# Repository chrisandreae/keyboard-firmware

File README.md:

# Programmable keyboard firmware
**(c) 2012-2014 Chris Andreae**

An extensively programmable USB keyboard firmware for AVR microcontrollers, easily adaptable to new keyboard hardware.

## Features

 * Dynamically reprogrammable two-layer layout (one for the main keyboard, and one for the keypad), with layer switching via a 'keypad' key
 * Also appears as USB mouse (whose functions can be bound to keys)
 * Onboard layout profiles to save/restore up to ten separate programmed
   keyboard layouts.
 * Buzzer audio support (included in Kinesis hardware)
 * USB API for configuring, remapping and uploading programs to the keyboard. (C++ Qt4-based GUI client and Ruby library included.)
 * Enhanced text macros that fully support modifier keys and can be triggered by any combination of up to four keys <sup>[*](#myfootnote1)</sup>
 * Programming, macro recording and layout backup save/load can be performed entirely on-keyboard with no additional software <sup>[*](#myfootnote1)</sup>
 * Built-in virtual machine interpreter for running up to six concurrent independent tasks <sup>[*](#myfootnote1)</sup>

<a name="myfootnote1">*</a>: This feature requires an external AT24C164 or compatible EEPROM (already built into Kinesis Advantage and Kinesis Advantage Pro keyboards).

## Currently Supported Keyboards

For now, the firmware supports various keyboard models:
 * Out of the box:
   * Ergodox
 * With drop-in microcontroller replacement (see schematic/ dir):
   * various Kinesis contoured ergonomic keyboards
     * Kinesis Contoured (tested on model 110; should also support models 100, 120 and 130)
     * Kinesis Advantage & Kinesis Advantage Pro (models 500 and 510)
 PR are welcome to extend support to other keyboards!

+### Drop-in microcontroller replacement
The drop-in microcontroller replacement can be built using most ATMega series AVR microcontrollers. The firmware accesses it via either LUFA (if native USB is available) or VUSB.

## Compiling

To compile the project for a non-USB-capable AVR using the V-USB library:

````make -f Makefile.vusb HARDWARE_VARIANT=<variant>````

Currently supported hardware variants for non-USB AVRs are:

* ````KINESIS```` (Kinesis Advantage/Professional, ATMega32, board design in schematic/Kinesis{Advantage/Professional})
* ````KINESIS110```` (Kinesis Model 110, ATMega32, board design in schematic/KinesisModel110)

To compile the project for a USB-capable AVR using the LUFA library:

````make -f Makefile.lufa HARDWARE_VARIANT=<variant> HAS_EXTERNAL_STORAGE={1,0}````

Currently supported hardware variants for USB AVRs are:

* ````ERGODOX```` (Ergodox, ATMega32u4 (Teensy))

## Usage

The default key layout for each hardware type can be found in the subdirectory ````layouts/````

### Enter/exit layout programming

Kinesis: ````Program + F12````

Ergodox: ````Program + P````

Press the above key combination to enter programming mode. In programming mode,
first press a source key to select the action of that key in the default
layout. Then, press a destination key to assign the selected action to. Repeat
source and destination keys as desired to continue remapping. The keypad key may
be pressed at any time to switch layers, in order to allow copying keys between
layers. The keypad and program keys may not be themselves remapped. When done,
press the above programming-mode key combination to leave programming mode.

### Layout backup saving/loading

* Save current layout to backup slot   = ````Progrm + S + [1 - 0]````
* Restore layout from backup slot      = ````Progrm + L + [1 - 0]````
* Delete saved layout from backup slot = ````Progrm + D + [1 - 0]````

In addition to the current layout, you can create up to 10 independent backup layouts.
Backup layouts allow you to rapidly switch between different keyboard mapping configurations.
Each backup layout slot is associated with a number key from ````1```` to ````0````. Layouts are
stored as their difference from the factory-default layout: the more keys that are
remapped from their default positions, the more space that a backup layout will consume.
In total, there is space for 256 key remappings shared between all backup layouts.

### Reset to default layout

Kinesis: ````Program + F7````

Ergodox: ````Program + Z````

Resets the current layout to the default. Saved layouts are not affected.

### Reset all customizations

Kinesis: ````Program + LShift + F7````

Ergodox: ````Program + LShift + Z````

Resets all keyboard customizations (current layout, saved layouts, macros, programs).

### Start/finish macro recording (Note: requires EEPROM)

Kinesis: ````Program + F11````

Ergodox: ````Program + M````

Press the above key combination to enter macro recording mode. Then, press and
release a combination of up to four keys as a trigger for the macro. Then, type
the contents of the macro. Macros are dynamically sized: you can define up to 50
macros, whose size in total must be under 1022 bytes (each key press or release
in the macro consumes one byte). To finish recording the macro, press the above
macro recording key combination again.

To delete a macro, enter macro recording mode, press the macro's trigger
combination, and then immediately exit macro mode by pressing the above macro
recording key combination.

### Enable/disable key click (Note: requires buzzer)

````Program + \````

When key-click is enabled, a noise will be each time the keyboard registers a
keypress. This can be useful to learn to type without 'bottoming-out' the keys.

### VM Programs (Note: requires EEPROM)

The keyboard includes a built in virtual machine interpreter which can run up to
six concurrent programs. A program is bound to a trigger combination like a
macro. Once the combination is pressed, the program starts executing and
continues until it finishes. Programs can inspect the state of the keyboard,
cause keys to be pressed and released, and perform other functions as documented
in the section **Compiler** below. Programs must be uploaded to the keyboard
using the client software as described in the section **GUI Client** below.

## GUI Client

The keyboard also supports a GUI client which uses USB vendor commands to
reprogram the keyboard. The client provides:

 * Layout viewing, remapping and resetting
 * Macro trigger editing and macro removal (macro body editing is yet to come)
 * Program uploading

The GUI client is written in C++/QT and requires libusb. Run ````qmake```` then
````make```` in the ````qtclient/```` subdirectory to build. A Ruby library is
also provided to communicate with the keyboard, in the ````ruby-client````
subdirectory.

## Compiler and Virtual Machine

The keyboard can run small compiled programs written in a C-like language. To
build the compiler, run `cabal build` in the ````compiler/```` subdirectory. The
GHC Haskell compiler is required to build.

To compile a program:
  ````keyc -oprogram.k program.kc````

See ````compiler/examples/```` for some example programs.

A program is a set of global variable and function declarations. A function
named ````main```` must be present.  Control structures are C-like (if, while,
for, return), however pointers, arrays and goto are not present. Additionally,
the ````exit```` keyword may be used to terminate the program at any time.

Local variables are lexically scoped, and declarations may hide global variables
or local variables in enclosing scopes.

The language features two signed types, ````byte```` (8-bit) and ````short````
(16-bit). Bytes may be automatically promoted (with sign extension) to shorts,
but to truncate a short to a byte requres a cast.  As in Java, unsigned values
may be provided using hexadecimal literals, but will be treated by arithmetic as
signed. Certain library functions expect unsigned values. Bare literals are
interpreted as bytes: to specify a short literal, append a ````s````.

Programs by default are run in very small stacks (48 bytes), so unbounded
recursion is not recommended. This can be increased on larger memory devices by
changing ````STACK_SIZE```` in interpreter.h.

The system library includes the following functions:

* ````void pressKey(byte h_keycode)````
  Causes the argument (unsigned byte) HID (not physical) key to be pressed. Does
  not return until a report has been sent.

* ````void releaseKey(byte h_keycode)````
  Causes the argument (unsigned byte) HID key to be released, if it was being
  pressed by this program.

* ````byte checkKey(byte h_keycode)````
  Checks the current state for any key mapped to the argument (unsigned byte) HID
  keycode, returns 1 or 0.

* ````byte checkPhysKey(byte p_keycode)````
  Checks the current state for the argument (unsigned byte) physical key. An
  argument of 0 means the the key that triggered the program. Returns 1 or 0.

* ````byte waitKey(byte key, short timeout)````
  Causes execution to be stopped until a key mapped to the argument (unsigned
  byte) HID keycode (or 0 for any key) has been pressed, or the argument time
  has elapsed (0 for indefinite).  Returns the mapped HID keycode of the first
  pressed key (not necessarily the argument) or 0 if timed out.

* ````byte waitPhysKey(byte key, short timeout)````
  Like waitKey(), but takes an argument physical keycode or 0 for the key that
  triggered the program. Returns 1 if pressed or 0 if timed out.

* ````void delay(short ms)````
  Causes execution to be stopped until argument milliseconds have elapsed

* ````short getUptimeMS()````
  Returns keyboard uptime in ms truncated to a signed short int

* ````short getUptime()````
  Returns keyboard uptime in seconds truncated to signed short int

* ````void buzz(short time)````
  Runs the buzzer for the next 'time' ms

* ````void buzzAt(short time, unsigned byte freq)````
  Runs the buzzer for the next 'time' ms at frequency (1/(4e-6 * freq)) Hz

* ````void moveMouse(byte x, byte y)````
  Moves the mouse by the requested offset next time the mouse report is sent. Does
  not return until report has been sent.

* ````void pressMouseButtons(byte buttonMask)````
  Presses the mouse buttons specified by buttonMask (bits 1-5 = buttons 1-5). Does
  not return until report has been sent.

* ````void releaseMouseButtons(byte buttonMask)````
  Releases the mouse buttons specified by buttonMask (bits 1-5 = buttons 1-5) if
  they are pressed by this program. Does not return until report has been sent.

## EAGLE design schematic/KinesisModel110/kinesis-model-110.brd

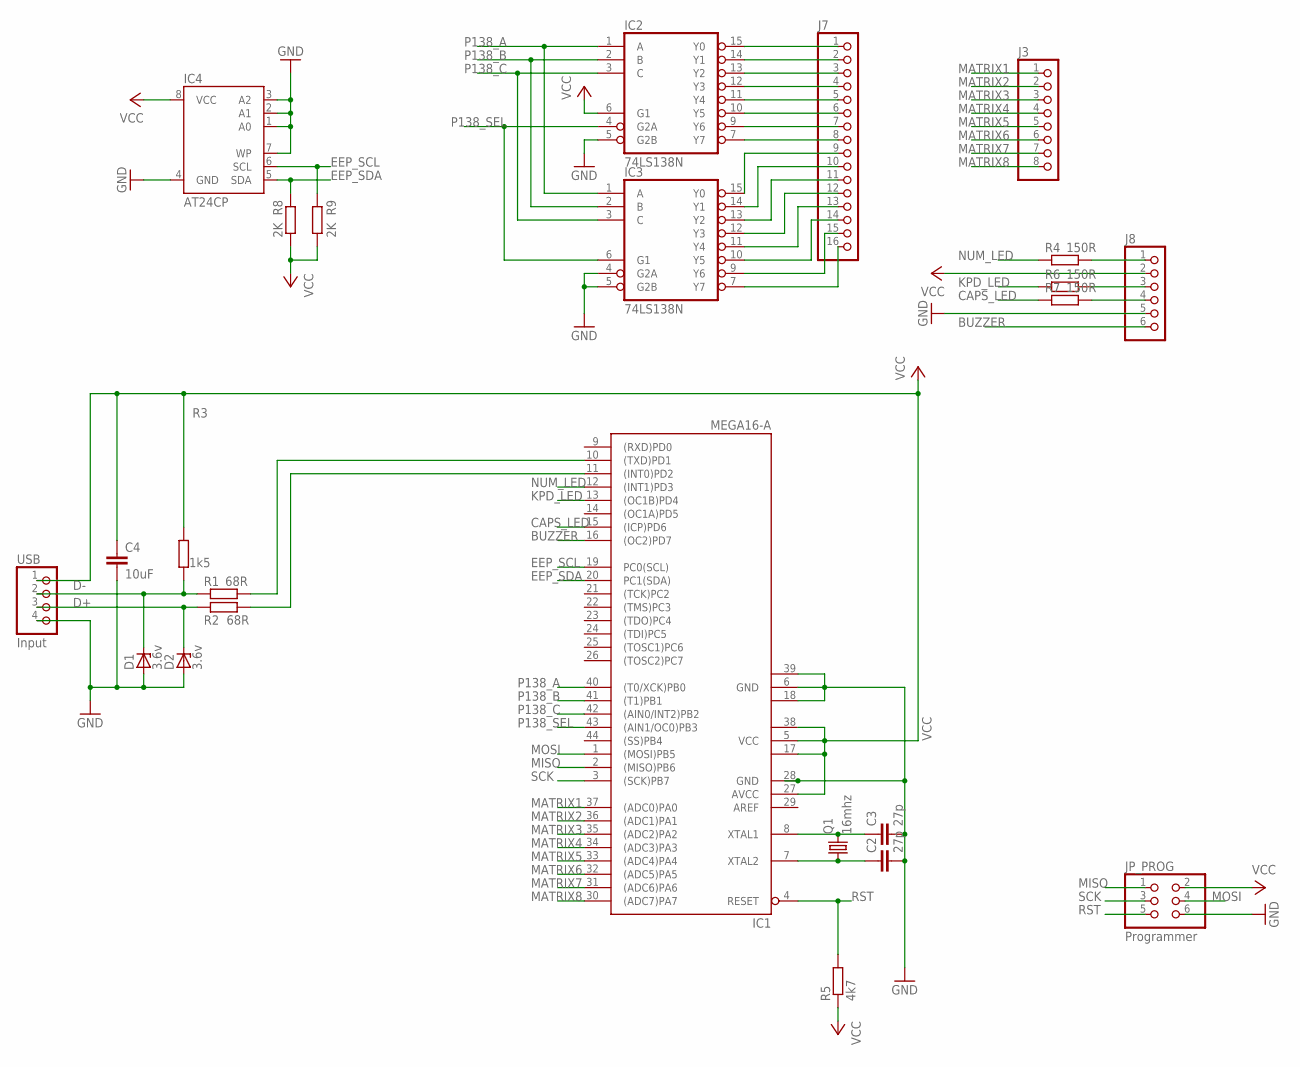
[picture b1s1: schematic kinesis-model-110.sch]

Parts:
C2, C3: 27p; C0603
C4: 10uF; C0805
D1, D2: 3.6v; SOD80C
IC1: MEGA16-A; TQFP44
IC2, IC3: 74LS138N; DIL16
IC4: AT24CP; DIL08
J3: PINHD-1X8; 1X08
J7: PINHD-1X16; 1X16
J8: PINHD-1X6; 1X06
JP_PROG: Programmer; 2X03
Q1: 16mhz; HC49/S
R1, R2: 68R; R0603
R3: 1k5; R0603
R4, R6, R7: 150R; R0603
R5: 4k7; R0603
R8, R9: 2K; R0603
USB: Input; 1X04

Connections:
BUZZER: IC1.16 ((OC2)PD7), J8.6
CAPS_LED: IC1.15 ((ICP)PD6), R7.1
CHIP-D+: IC1.11 ((INT0)PD2), R2.2
CHIP-D-: IC1.10 ((TXD)PD1), R1.2
D+: D2.C, R2.1, USB.3
D-: D1.C, R1.1, R3.1, USB.2
EEP_SCL: IC1.19 (PC0(SCL)), IC4.6 (SCL), R9.1
EEP_SDA: IC1.20 (PC1(SDA)), IC4.5 (SDA), R8.1
GND: C2.2, C3.2, C4.2, D1.A, D2.A, IC1.6 (GND), IC1.18 (GND1), IC1.28 (GND), IC1.39 (GND2), IC2.5 (G2B), IC2.8 (GND), IC3.4 (G2A), IC3.5 (G2B), IC3.8 (GND), IC4.1 (A0), IC4.2 (A1), IC4.3 (A2), IC4.4 (GND), IC4.7 (WP), J8.5, JP_PROG.6, USB.4
KPD_LED: IC1.13 ((OC1B)PD4), R6.1
MATRIX1: IC1.37 ((ADC0)PA0), J3.1
MATRIX2: IC1.36 ((ADC1)PA1), J3.2
MATRIX3: IC1.35 ((ADC2)PA2), J3.3
MATRIX4: IC1.34 ((ADC3)PA3), J3.4
MATRIX5: IC1.33 ((ADC4)PA4), J3.5
MATRIX6: IC1.32 ((ADC5)PA5), J3.6
MATRIX7: IC1.31 ((ADC6)PA6), J3.7
MATRIX8: IC1.30 ((ADC7)PA7), J3.8
MISO: IC1.2 ((MISO)PB6), JP_PROG.1
MOSI: IC1.1 ((MOSI)PB5), JP_PROG.4
unnamed: IC2.15 (Y0), J7.1
unnamed: IC2.14 (Y1), J7.2
unnamed: IC2.13 (Y2), J7.3
unnamed: IC2.12 (Y3), J7.4
unnamed: IC2.11 (Y4), J7.5
unnamed: IC2.10 (Y5), J7.6
unnamed: IC2.9 (Y6), J7.7
unnamed: IC2.7 (Y7), J7.8
unnamed: IC3.15 (Y0), J7.9
unnamed: IC3.14 (Y1), J7.10
unnamed: IC3.13 (Y2), J7.11
unnamed: IC3.12 (Y3), J7.12
unnamed: IC3.11 (Y4), J7.13
unnamed: IC3.10 (Y5), J7.14
unnamed: IC3.9 (Y6), J7.15
unnamed: IC3.7 (Y7), J7.16
unnamed: J8.1, R4.2
unnamed: J8.3, R6.2
unnamed: J8.4, R7.2
NUM_LED: IC1.12 ((INT1)PD3), R4.1
P138_A: IC1.40 ((T0/XCK)PB0), IC2.1 (A), IC3.1 (A)
P138_B: IC1.41 ((T1)PB1), IC2.2 (B), IC3.2 (B)
P138_C: IC1.42 ((AIN0/INT2)PB2), IC2.3 (C), IC3.3 (C)
P138_SEL: IC1.43 ((AIN1/OC0)PB3), IC2.4 (G2A), IC3.6 (G1)
PIN9: C2.1, IC1.7 (XTAL2), Q1.1
PIN10: C3.1, IC1.8 (XTAL1), Q1.2
RST: IC1.4 (RESET), JP_PROG.5, R5.2
SCK: IC1.3 ((SCK)PB7), JP_PROG.3
VCC: C4.1, IC1.5 (VCC), IC1.17 (VCC1), IC1.27 (AVCC), IC1.38 (VCC2), IC2.6 (G1), IC2.16 (VCC), IC3.16 (VCC), IC4.8 (VCC), J8.2, JP_PROG.2, R3.2, R5.1, R8.2, R9.2, USB.1

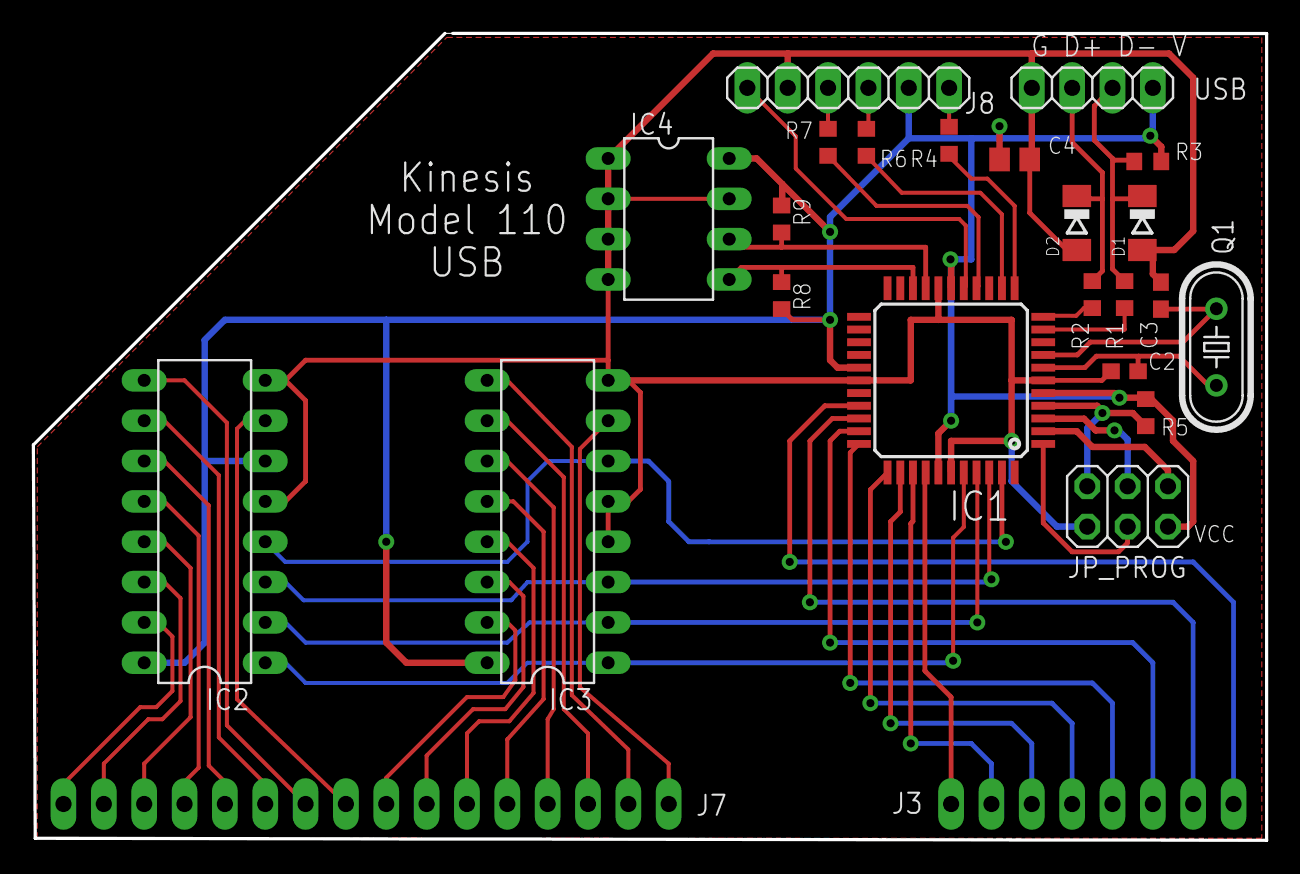
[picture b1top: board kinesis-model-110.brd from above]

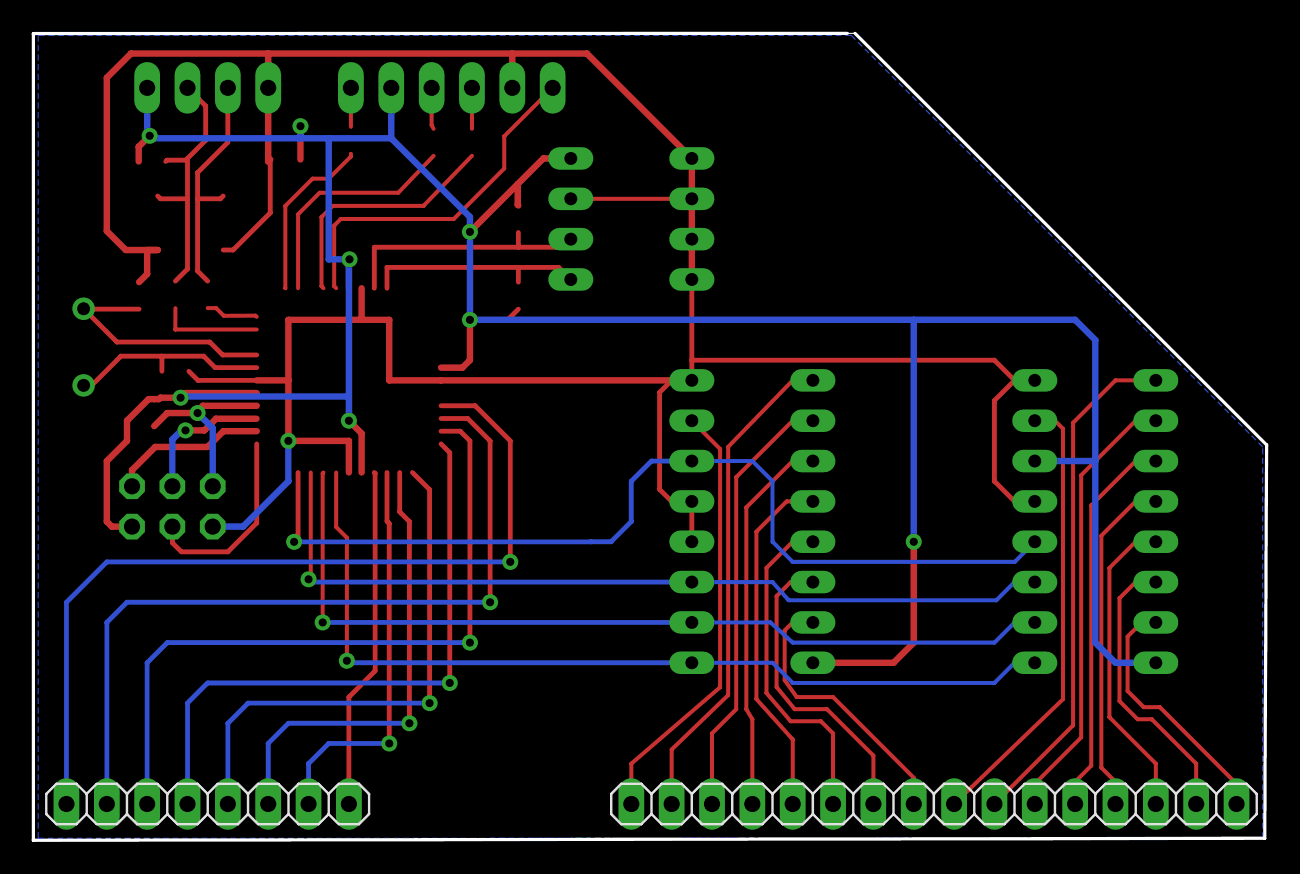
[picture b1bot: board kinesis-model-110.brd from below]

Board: 2 copper layers, 77.6 x 50.8 mm, 24 parts (2 on the bottom side), 49 nets.

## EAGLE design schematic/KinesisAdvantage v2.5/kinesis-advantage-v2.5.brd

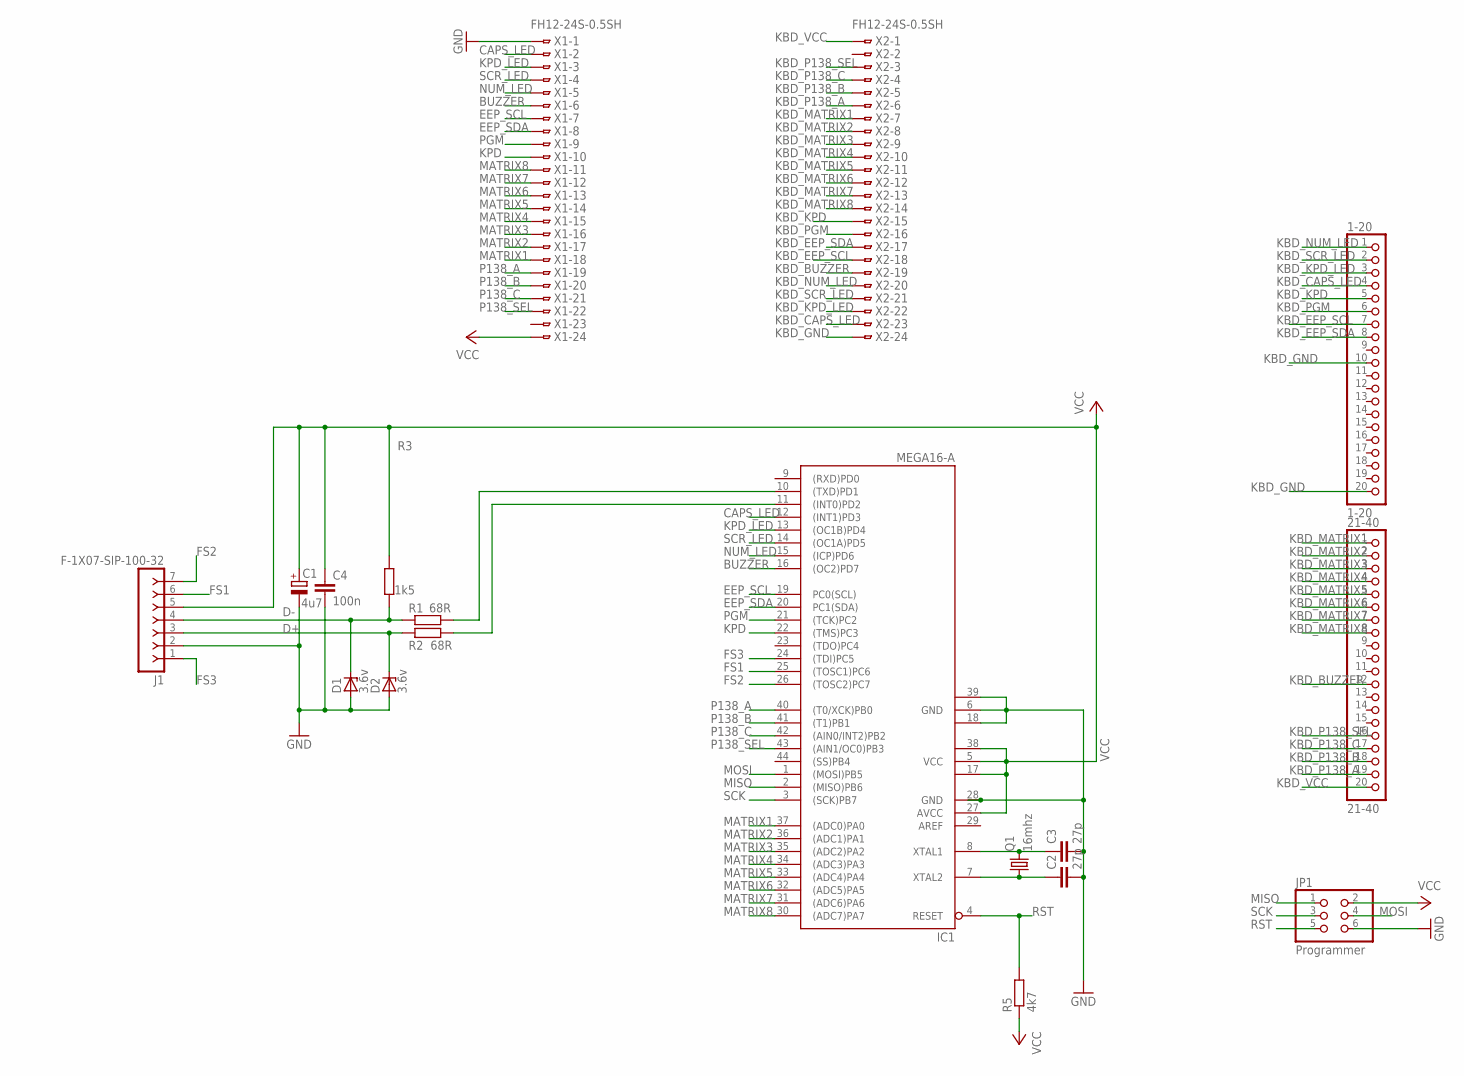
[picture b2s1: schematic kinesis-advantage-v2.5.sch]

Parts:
1-20: 1-20; 1X20-BIG
21-40: 21-40; 1X20-BIG
C1: 4u7; E2-5
C2, C3: 27p; C0603
C4: 100n; C0603
D1, D2: 3.6v; SOD80C
IC1: MEGA16-A; TQFP44
J1: F-1X07-SIP-100-32; SIP-100-07-32
JP1: Programmer; 2X03
Q1: 16mhz; HC49/S
R1, R2: 68R; R0603
R3: 1k5; R0603
R5: 4k7; R0603
X1, X2: FH12-24S-0.5SH

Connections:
BUZZER: IC1.16 ((OC2)PD7), X1.6
CAPS_LED: IC1.12 ((INT1)PD3), X1.2
CHIP-D+: IC1.11 ((INT0)PD2), R2.2
CHIP-D-: IC1.10 ((TXD)PD1), R1.2
D+: D2.C, J1.3, R2.1
D-: D1.C, J1.4, R1.1, R3.1
EEP_SCL: IC1.19 (PC0(SCL)), X1.7
EEP_SDA: IC1.20 (PC1(SDA)), X1.8
FS1: IC1.25 ((TOSC1)PC6), J1.6
FS2: IC1.26 ((TOSC2)PC7), J1.7
FS3: IC1.24 ((TDI)PC5), J1.1
GND: C1.-, C2.2, C3.2, C4.2, D1.A, D2.A, IC1.6 (GND), IC1.18 (GND1), IC1.28 (GND), IC1.39 (GND2), J1.2, JP1.6, X1.1
KBD_BUZZER: 21-40.12, X2.19
KBD_CAPS_LED: 1-20.4, X2.23
KBD_EEP_SCL: 1-20.7, X2.18
KBD_EEP_SDA: 1-20.8, X2.17
KBD_GND: 1-20.10, 1-20.20, X2.24
KBD_KPD: 1-20.5, X2.15
KBD_KPD_LED: 1-20.3, X2.22
KBD_MATRIX1: 21-40.1, X2.7
KBD_MATRIX2: 21-40.2, X2.8
KBD_MATRIX3: 21-40.3, X2.9
KBD_MATRIX4: 21-40.4, X2.10
KBD_MATRIX5: 21-40.5, X2.11
KBD_MATRIX6: 21-40.6, X2.12
KBD_MATRIX7: 21-40.7, X2.13
KBD_MATRIX8: 21-40.8, X2.14
KBD_NUM_LED: 1-20.1, X2.20
KBD_P138_A: 21-40.19, X2.6
KBD_P138_B: 21-40.18, X2.5
KBD_P138_C: 21-40.17, X2.4
KBD_P138_SEL: 21-40.16, X2.3
KBD_PGM: 1-20.6, X2.16
KBD_SCR_LED: 1-20.2, X2.21
KBD_VCC: 21-40.20, X2.1
KPD: IC1.22 ((TMS)PC3), X1.10
KPD_LED: IC1.13 ((OC1B)PD4), X1.3
MATRIX1: IC1.37 ((ADC0)PA0), X1.18
MATRIX2: IC1.36 ((ADC1)PA1), X1.17
MATRIX3: IC1.35 ((ADC2)PA2), X1.16
MATRIX4: IC1.34 ((ADC3)PA3), X1.15
MATRIX5: IC1.33 ((ADC4)PA4), X1.14
MATRIX6: IC1.32 ((ADC5)PA5), X1.13
MATRIX7: IC1.31 ((ADC6)PA6), X1.12
MATRIX8: IC1.30 ((ADC7)PA7), X1.11
MISO: IC1.2 ((MISO)PB6), JP1.1
MOSI: IC1.1 ((MOSI)PB5), JP1.4
NUM_LED: IC1.15 ((ICP)PD6), X1.5
P138_A: IC1.40 ((T0/XCK)PB0), X1.19
P138_B: IC1.41 ((T1)PB1), X1.20
P138_C: IC1.42 ((AIN0/INT2)PB2), X1.21
P138_SEL: IC1.43 ((AIN1/OC0)PB3), X1.22
PGM: IC1.21 ((TCK)PC2), X1.9
PIN9: C2.1, IC1.7 (XTAL2), Q1.1
PIN10: C3.1, IC1.8 (XTAL1), Q1.2
RST: IC1.4 (RESET), JP1.5, R5.2
SCK: IC1.3 ((SCK)PB7), JP1.3
SCR_LED: IC1.14 ((OC1A)PD5), X1.4
VCC: C1.+, C4.1, IC1.5 (VCC), IC1.17 (VCC1), IC1.27 (AVCC), IC1.38 (VCC2), J1.5, JP1.2, R3.2, R5.1, X1.24

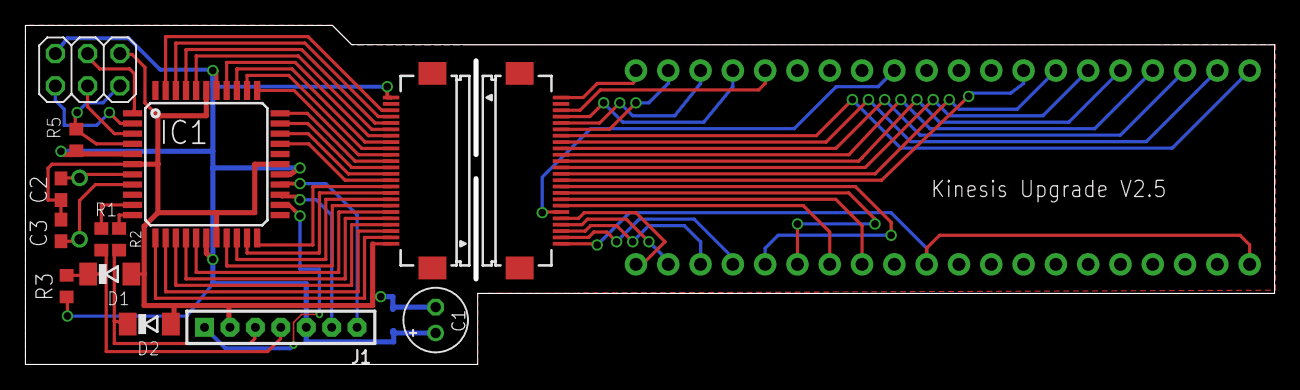
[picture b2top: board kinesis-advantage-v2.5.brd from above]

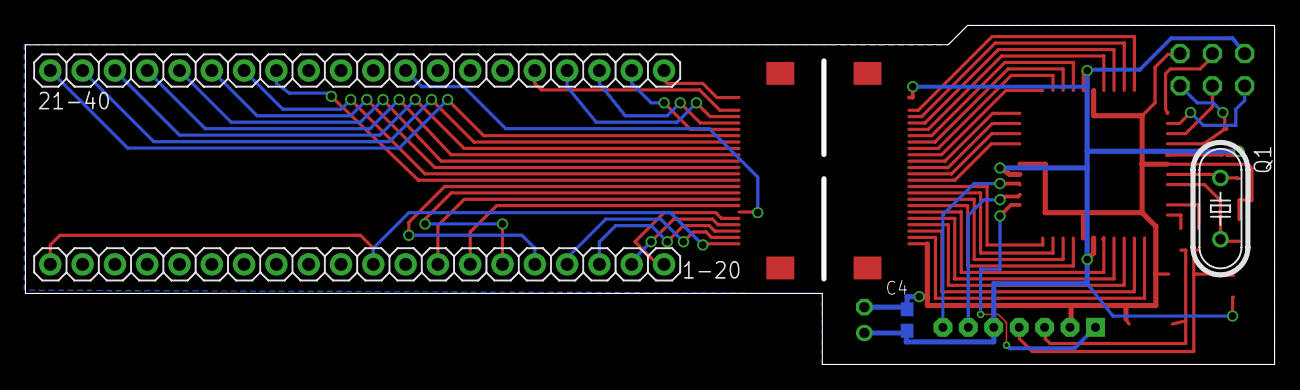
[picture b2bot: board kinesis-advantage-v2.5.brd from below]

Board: 2 copper layers, 97.8 x 26.3 mm, 18 parts (4 on the bottom side), 59 nets.

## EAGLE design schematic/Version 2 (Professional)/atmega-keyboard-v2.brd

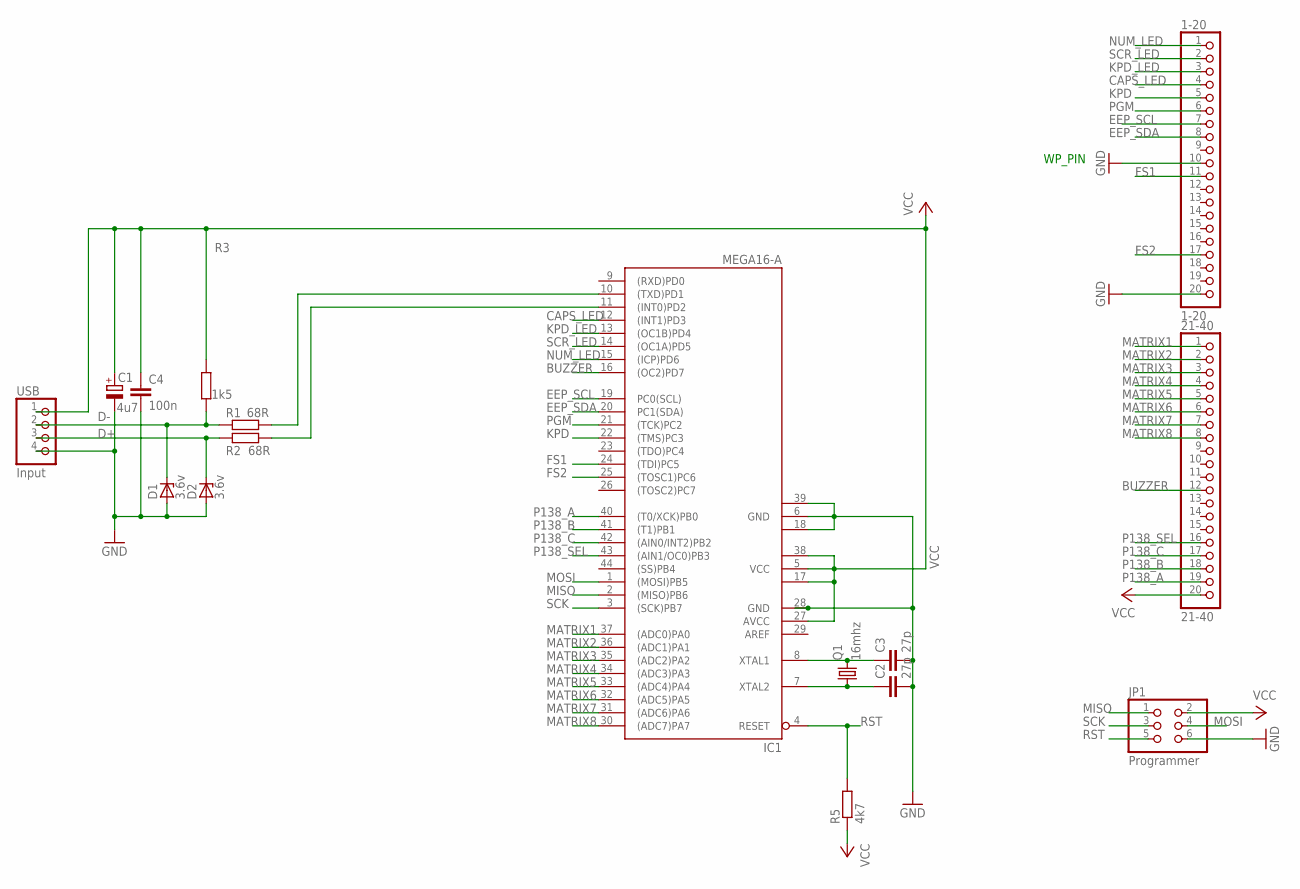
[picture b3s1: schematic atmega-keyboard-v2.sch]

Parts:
1-20: 1-20; 1X20
21-40: 21-40; 1X20
C1: 4u7; E2-5
C2, C3: 27p; C0805
C4: 100n; C0805
D1, D2: 3.6v; SOD80C
IC1: MEGA16-A; TQFP44
JP1: Programmer; 2X03
Q1: 16mhz; HC49/S
R1, R2: 68R; R0805
R3: 1k5; R0805
R5: 4k7; R0805
USB: Input; 1X04

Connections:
BUZZER: 21-40.12, IC1.16 ((OC2)PD7)
CAPS_LED: 1-20.4, IC1.12 ((INT1)PD3)
CHIP-D+: IC1.11 ((INT0)PD2), R2.2
CHIP-D-: IC1.10 ((TXD)PD1), R1.2
D+: D2.C, R2.1, USB.3
D-: D1.C, R1.1, R3.1, USB.2
EEP_SCL: 1-20.7, IC1.19 (PC0(SCL))
EEP_SDA: 1-20.8, IC1.20 (PC1(SDA))
FS1: 1-20.11, IC1.24 ((TDI)PC5)
FS2: 1-20.17, IC1.25 ((TOSC1)PC6)
GND: 1-20.10, 1-20.20, C1.-, C2.2, C3.2, C4.2, D1.A, D2.A, IC1.6 (GND), IC1.18 (GND1), IC1.28 (GND), IC1.39 (GND2), JP1.6, USB.4
KPD: 1-20.5, IC1.22 ((TMS)PC3)
KPD_LED: 1-20.3, IC1.13 ((OC1B)PD4)
MATRIX1: 21-40.1, IC1.37 ((ADC0)PA0)
MATRIX2: 21-40.2, IC1.36 ((ADC1)PA1)
MATRIX3: 21-40.3, IC1.35 ((ADC2)PA2)
MATRIX4: 21-40.4, IC1.34 ((ADC3)PA3)
MATRIX5: 21-40.5, IC1.33 ((ADC4)PA4)
MATRIX6: 21-40.6, IC1.32 ((ADC5)PA5)
MATRIX7: 21-40.7, IC1.31 ((ADC6)PA6)
MATRIX8: 21-40.8, IC1.30 ((ADC7)PA7)
MISO: IC1.2 ((MISO)PB6), JP1.1
MOSI: IC1.1 ((MOSI)PB5), JP1.4
NUM_LED: 1-20.1, IC1.15 ((ICP)PD6)
P138_A: 21-40.19, IC1.40 ((T0/XCK)PB0)
P138_B: 21-40.18, IC1.41 ((T1)PB1)
P138_C: 21-40.17, IC1.42 ((AIN0/INT2)PB2)
P138_SEL: 21-40.16, IC1.43 ((AIN1/OC0)PB3)
PGM: 1-20.6, IC1.21 ((TCK)PC2)
PIN9: C2.1, IC1.7 (XTAL2), Q1.1
PIN10: C3.1, IC1.8 (XTAL1), Q1.2
RST: IC1.4 (RESET), JP1.5, R5.2
SCK: IC1.3 ((SCK)PB7), JP1.3
SCR_LED: 1-20.2, IC1.14 ((OC1A)PD5)
VCC: 21-40.20, C1.+, C4.1, IC1.5 (VCC), IC1.17 (VCC1), IC1.27 (AVCC), IC1.38 (VCC2), JP1.2, R3.2, R5.1, USB.1

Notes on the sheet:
WP_PIN

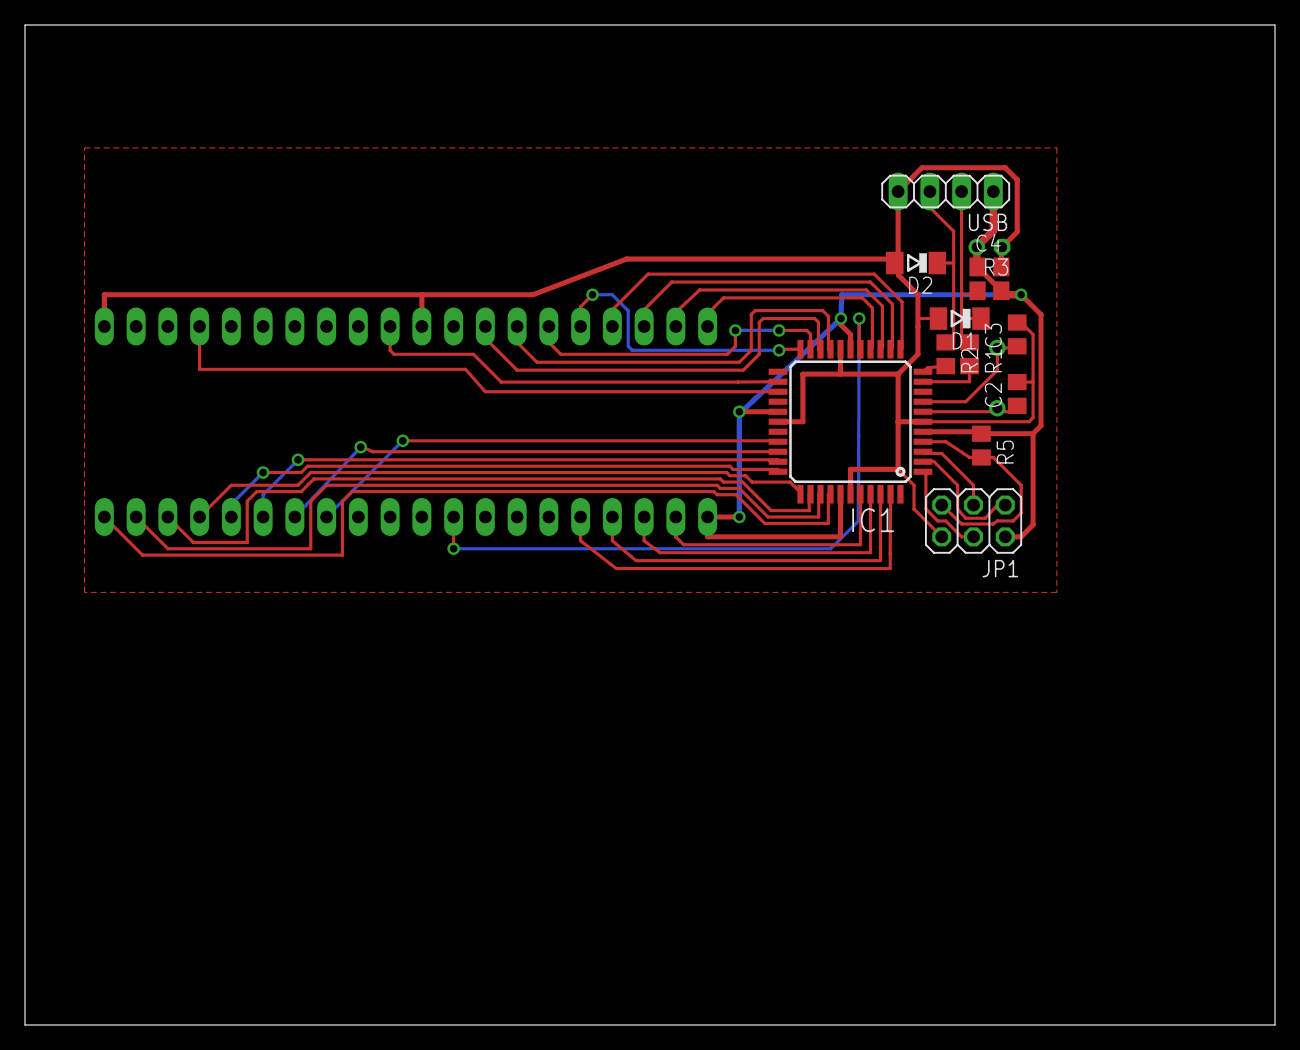
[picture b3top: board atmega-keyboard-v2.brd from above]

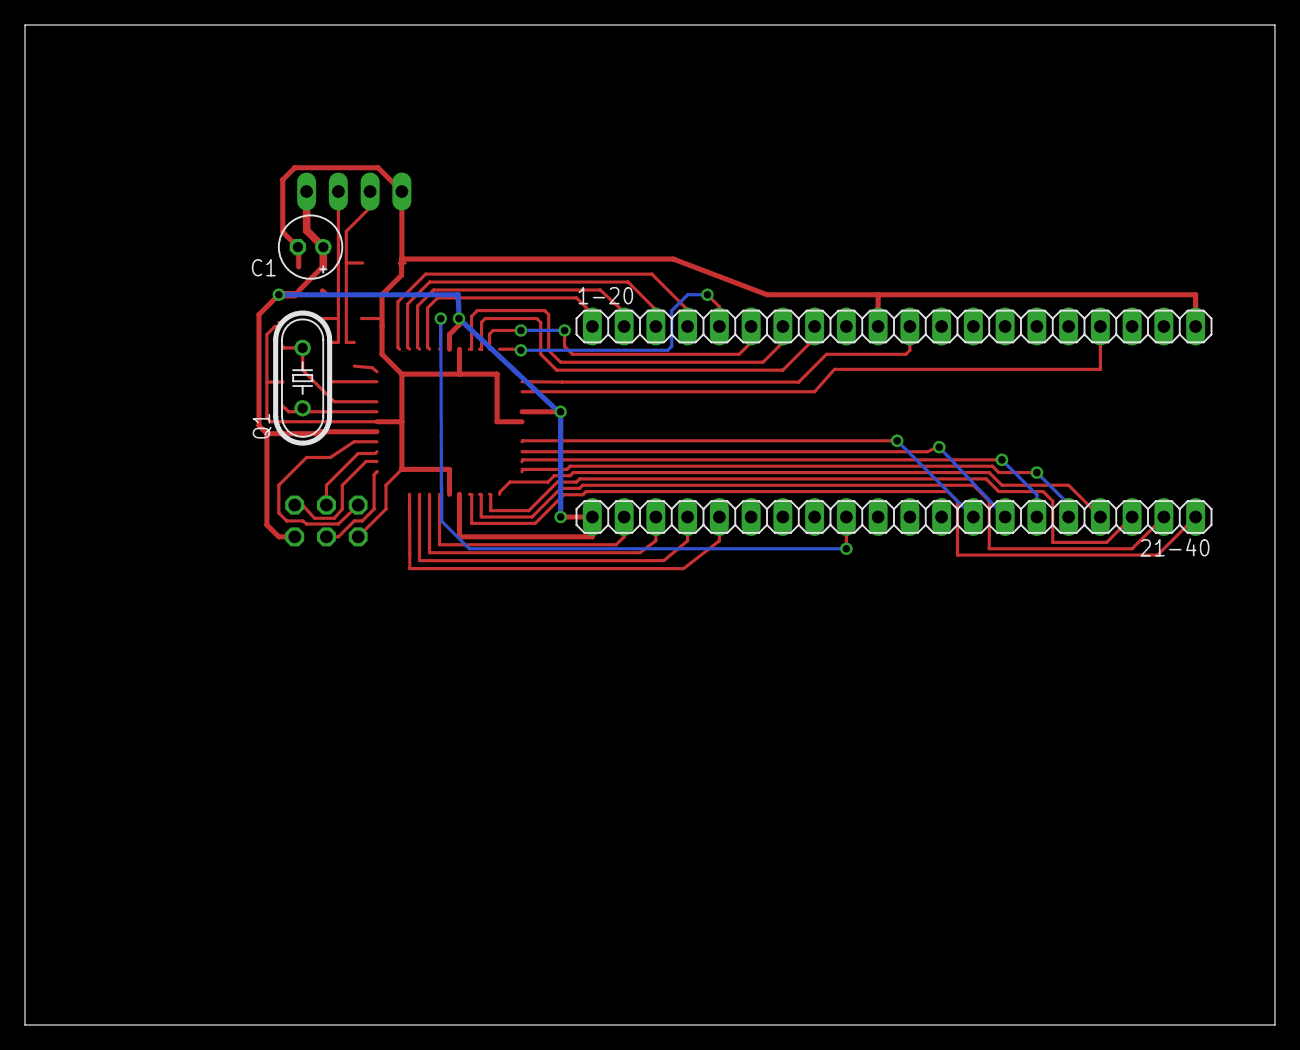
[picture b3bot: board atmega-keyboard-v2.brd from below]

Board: 2 copper layers, 100.0 x 80.0 mm, 16 parts (4 on the bottom side), 35 nets.

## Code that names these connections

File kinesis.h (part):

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//    foot switch 2 (pin 17) - (note that these may differ on the 3-foot-switch Advantage models)

// output:
//    4 LEDs (pins 1-4, sink current to enable) (num=1, scrolllock=2, kpd=3, caps=4)
//    buzzer (pin 32)

// EEPROM access:
//  have access to up to two AT24C164 2kb serial eeproms via pins 7 and
//  8, connected to SCL and SDA respectively with external pull-ups.
//  The eeproms have their addresse lines tied to 000 and 001 respectively.
//         WP  (write protect) (pin10) = connected to WP pin of eeprom, must be low to enable.
//                                       (Note that this is also connected to the demultiplexers: most convenient to just tie it permanently to ground)
//         SCL (serial eeprom clock line) (pin7)
//         SDA (serial eeprom data line) (pin8)
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#if defined(__AVR_ATmega16A__)
// Original board layout (v1)

// PD4 = USB D-
// PD2 = USB D+

#define MATRIX_PORT PORTB
#define MATRIX_DDR  DDRB
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#define INPUT_PIN6_DDR  DDRC
#define INPUT_PIN6 (1<<0)

// FS1 and FS2 are PC5 and PC6

#define INPUT_REST_PIN  PINA
#define INPUT_REST_PORT PORTA
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#define LED_KEYPAD (1<<5)
#define ALL_LEDS (LED_CAPS | LED_NUMLOCK | LED_SCROLLLOCK | LED_KEYPAD)

#define USE_BUZZER 0 // new buzzer code uses OC2 pin, not compatible with this board layout

#define BUZZER_PORT PORTC
#define BUZZER_DDR DDRC
#define BUZZER (1<<3)

#define BITBANG_TWI // original board bitbangs TWI, doesn't use hardware I2C pins

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#elif defined(__AVR_ATmega32__)
// New board layout (v2)

// PD4 = USB D-
// PD2 = USB D+

#define MATRIX_PORT PORTB
#define MATRIX_DDR  DDRB
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#define INPUT_PIN6_DDR  DDRC
#define INPUT_PIN6 (1<<2)

// FS1 and FS2 are PC5 and PC6

#define INPUT_REST_PIN  PINA
#define INPUT_REST_PORT PORTA
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
#define USE_BUZZER 1

#define BUZZER_PORT PORTD
#define BUZZER_DDR DDRD
#define BUZZER (1<<7)

#define EEPROM_PORT PORTC
#define EEPROM_DDR  DDRC
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
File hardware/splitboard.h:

/*
  Kinesis ergonomic keyboard firmware replacement

  Copyright 2012 Chris Andreae (chris (at) andreae.gen.nz)

  Licensed under the GNU GPL v2 (see GPL2.txt).

  ==========================

  If built for V-USB, this program includes library and sample code from:
	 V-USB, (C) Objective Development Software GmbH
	 Licensed under the GNU GPL v2 (see GPL2.txt)

  ==========================

  If built for LUFA, this program includes library and sample code from:
			 LUFA Library
	 Copyright (C) Dean Camera, 2011.

  dean [at] fourwalledcubicle [dot] com
		   www.lufa-lib.org

  Copyright 2011  Dean Camera (dean [at] fourwalledcubicle [dot] com)

  Permission to use, copy, modify, distribute, and sell this
  software and its documentation for any purpose is hereby granted
  without fee, provided that the above copyright notice appear in
  all copies and that both that the copyright notice and this
  permission notice and warranty disclaimer appear in supporting
  documentation, and that the name of the author not be used in
  advertising or publicity pertaining to distribution of the
  software without specific, written prior permission.

  The author disclaim all warranties with regard to this
  software, including all implied warranties of merchantability
  and fitness.  In no event shall the author be liable for any
  special, indirect or consequential damages or any damages
  whatsoever resulting from loss of use, data or profits, whether
  in an action of contract, negligence or other tortious action,
  arising out of or in connection with the use or performance of
  this software.
*/

#ifndef __KEYPAD_H
#define __KEYPAD_H

#include "keystate.h"

// Use Obdev's free usb id for keyboards discriminated by serial number
#define USB_VENDOR_ID  0x16c0
#define USB_PRODUCT_ID 0x27dc // Should be b! hacky

// But define different descriptive strings
#define USB_MANUFACTURER_STRING L"andreae.gen.nz"
#define USB_PRODUCT_STRING L"Programmable USB Splitboard"
#define USB_SERIAL_NUMBER_STRING L"andreae.gen.nz:splitboard"

// Unique identifier representing this keyboard's layout and
// definition of logical_keycode values.  Is reported to the
// configuration program over USB to identify the layout.
#define LAYOUT_ID 3

/* Storage layout */
#define CONSTANT_STORAGE           avr_pgm
#define MAPPING_STORAGE            avr_eeprom

#define SAVED_MAPPING_STORAGE      avr_eeprom
#define SAVED_MAPPING_COUNT        128          // 2-byte entries
#define MACRO_INDEX_STORAGE        avr_eeprom
#define MACRO_INDEX_COUNT          10           // 6-byte entries
#define MACROS_STORAGE             avr_eeprom
#define MACROS_SIZE                256
#define PROGRAM_STORAGE            avr_eeprom
#define PROGRAM_SIZE               256
#define PROGRAM_COUNT              2

#define NUM_PHYSICAL_KEYS 8 * 6 * 2
#define NUM_LOGICAL_KEYS  NUM_PHYSICAL_KEYS * 2
#define KEYPAD_LAYER_SIZE NUM_PHYSICAL_KEYS

// Describes an ergodox-esque keyboard made up of two 8x8 matrixes driven
// simultaneously via a pair of 164/165 shift registers.

#define MATRIX_ROWS 8  // Drive side. On this keyboard, actually columns.
#define MATRIX_COLS 16 // Read side.  On this keyboard, actually rows.

// Logical keys we have: logical keys represent a key-position+keypad-layer combination.
enum logical_keys {
	LOGICAL_KEY_RHS_TP1,
	LOGICAL_KEY_RHS_TP2,
	LOGICAL_KEY_RHS_TP3,
	LOGICAL_KEY_RHS_TP4,
	LOGICAL_KEY_RHS_TP5,
	LOGICAL_KEY_RHS_TP6,
	LOGICAL_KEY_RHS_C1R1,
	LOGICAL_KEY_RHS_C1R2,
	LOGICAL_KEY_RHS_C1R3,
	LOGICAL_KEY_RHS_C1R4,
	LOGICAL_KEY_RHS_C1R5,
	LOGICAL_KEY_RHS_C1R6,
	LOGICAL_KEY_RHS_C2R1,
	LOGICAL_KEY_RHS_C2R2,
	LOGICAL_KEY_RHS_C2R3,
	LOGICAL_KEY_RHS_C2R4,
	LOGICAL_KEY_RHS_C2R5,
	LOGICAL_KEY_RHS_C2R6,
	LOGICAL_KEY_RHS_C3R1,
	LOGICAL_KEY_RHS_C3R2,
	LOGICAL_KEY_RHS_C3R3,
	LOGICAL_KEY_RHS_C3R4,
	LOGICAL_KEY_RHS_C3R5,
	LOGICAL_KEY_RHS_C3R6,
	LOGICAL_KEY_RHS_C4R1,
	LOGICAL_KEY_RHS_C4R2,
	LOGICAL_KEY_RHS_C4R3,
	LOGICAL_KEY_RHS_C4R4,
	LOGICAL_KEY_RHS_C4R5,
	LOGICAL_KEY_RHS_C4R6,
	LOGICAL_KEY_RHS_C5R1,
	LOGICAL_KEY_RHS_C5R2,
	LOGICAL_KEY_RHS_C5R3,
	LOGICAL_KEY_RHS_C5R4,
	LOGICAL_KEY_RHS_C5R5,
	LOGICAL_KEY_RHS_C5R6,
	LOGICAL_KEY_RHS_C6R1,
	LOGICAL_KEY_RHS_C6R2,
	LOGICAL_KEY_RHS_C6R3,
	LOGICAL_KEY_RHS_C6R4,
	LOGICAL_KEY_RHS_C6R5,
	LOGICAL_KEY_RHS_C6R6,
	LOGICAL_KEY_RHS_C7R1,
	LOGICAL_KEY_RHS_C7R2,
	LOGICAL_KEY_RHS_C7R3,
	LOGICAL_KEY_RHS_C7R4,
	LOGICAL_KEY_RHS_C7R5,
	LOGICAL_KEY_RHS_C7R6,

	LOGICAL_KEY_LHS_TP1,
	LOGICAL_KEY_LHS_TP2,
	LOGICAL_KEY_LHS_TP3,
	LOGICAL_KEY_LHS_TP4,
	LOGICAL_KEY_LHS_TP5,
	LOGICAL_KEY_LHS_TP6,
	LOGICAL_KEY_LHS_C1R1,
	LOGICAL_KEY_LHS_C1R2,
	LOGICAL_KEY_LHS_C1R3,
	LOGICAL_KEY_LHS_C1R4,
	LOGICAL_KEY_LHS_C1R5,
	LOGICAL_KEY_LHS_C1R6,
	LOGICAL_KEY_LHS_C2R1,
	LOGICAL_KEY_LHS_C2R2,
	LOGICAL_KEY_LHS_C2R3,
	LOGICAL_KEY_LHS_C2R4,
	LOGICAL_KEY_LHS_C2R5,
	LOGICAL_KEY_LHS_C2R6,
	LOGICAL_KEY_LHS_C3R1,
	LOGICAL_KEY_LHS_C3R2,
	LOGICAL_KEY_LHS_C3R3,
	LOGICAL_KEY_LHS_C3R4,
	LOGICAL_KEY_LHS_C3R5,
	LOGICAL_KEY_LHS_C3R6,
	LOGICAL_KEY_LHS_C4R1,
	LOGICAL_KEY_LHS_C4R2,
	LOGICAL_KEY_LHS_C4R3,
	LOGICAL_KEY_LHS_C4R4,
	LOGICAL_KEY_LHS_C4R5,
	LOGICAL_KEY_LHS_C4R6,
	LOGICAL_KEY_LHS_C5R1,
	LOGICAL_KEY_LHS_C5R2,
	LOGICAL_KEY_LHS_C5R3,
	LOGICAL_KEY_LHS_C5R4,
	LOGICAL_KEY_LHS_C5R5,
	LOGICAL_KEY_LHS_C5R6,
	LOGICAL_KEY_LHS_C6R1,
	LOGICAL_KEY_LHS_C6R2,
	LOGICAL_KEY_LHS_C6R3,
	LOGICAL_KEY_LHS_C6R4,
	LOGICAL_KEY_LHS_C6R5,
	LOGICAL_KEY_LHS_C6R6,
	LOGICAL_KEY_LHS_C7R1,
	LOGICAL_KEY_LHS_C7R2,
	LOGICAL_KEY_LHS_C7R3,
	LOGICAL_KEY_LHS_C7R4,
	LOGICAL_KEY_LHS_C7R5,
	LOGICAL_KEY_LHS_C7R6,
	// The keypad layer duplicates the previous 16 keys
};

// Which logical keys to use for special in-built combinations
#define SPECIAL_HKEY_MACRO_RECORD  HID_KEYBOARD_SC_F7
#define SPECIAL_HKEY_REMAP         HID_KEYBOARD_SC_F8
#define SPECIAL_HKEY_REBOOT        HID_KEYBOARD_SC_F5
#define SPECIAL_HKEY_RESET_CONFIG  HID_KEYBOARD_SC_F4
#define SPECIAL_HKEY_RESET_FULLY   HID_KEYBOARD_SC_LEFT_SHIFT

extern const logical_keycode matrix_to_logical_map[MATRIX_ROWS][MATRIX_COLS] PROGMEM;

/* For each key, maps an index position to a default HID key code. */
/* stored in flash. */
extern const hid_keycode logical_to_hid_map_default[NUM_LOGICAL_KEYS] PROGMEM;


//////////////////////////////////////////////////////////////////////////////////////
// Board layout

// Using an Arduino Pro Micro and a pair of serial-to-parallel (164) and
// parallel-to-serial (165) shift registers.

// Pin 9 (PB5) - P2S parallel load (!PL: pin 1), S2P serial input (DSA: pin 1) (W6)
// Pin 8 (PB4) - P2S clock (CP: pin 2)                                         (W7)
// Pin 7 (PE6) - RHS P2S output (Q7: pin 9)                                    (W3)
// Pin 6 (PD7) - S2P clock (CP: pin 8)                                         (W9)
// Pin 5 (PC6) - LHS P2S output (Q7: pin 9)                                    (W8)

// Output: built in LED on PD5, sink current to enable

// No buzzer, no eeprom.
//////////////////////////////////////////////////////////////////////////////////////

#define P2S_LOAD_S2P_SER_PORT PORTB
#define P2S_LOAD_S2P_SER_DDR  DDRB
#define P2S_LOAD_S2P_SER_MASK (1<<5)

#define P2S_CLOCK_PORT PORTB
#define P2S_CLOCK_DDR  DDRB
#define P2S_CLOCK_MASK (1<<4)

#define RHS_P2S_DATA_PIN  PINE
#define RHS_P2S_DATA_PORT PORTE
#define RHS_P2S_DATA_DDR  DDRE
#define RHS_P2S_DATA_MASK (1<<6)

#define LHS_P2S_DATA_PIN  PINC
#define LHS_P2S_DATA_PORT PORTC
#define LHS_P2S_DATA_DDR  DDRC
#define LHS_P2S_DATA_MASK (1<<6)

#define S2P_CLOCK_PORT PORTD
#define S2P_CLOCK_DDR  DDRD
#define S2P_CLOCK_MASK (1<<7)

#define USE_BUZZER 0

#define LED_PORT PORTD
#define LED_DDR  DDRD
#define LED_CAPS (1<<5)
#define ALL_LEDS (LED_CAPS)

void ports_init(void);

/**
 * Gets the current physical input for a given physical position
 */
void matrix_select_row(uint8_t matrix_row);
uint8_t matrix_read_column(uint8_t matrix_column);

/* Macros: */
/** LED mask for the library LED driver, to indicate that the USB interface is not ready. */
#define LEDMASK_USB_NOTREADY     (LED_CAPS)

/** LED mask for the library LED driver, to indicate that the USB interface is enumerating. */
#define LEDMASK_USB_ENUMERATING  (LED_CAPS)

/** LED mask for the library LED driver, to indicate that the USB interface is ready. */
#define LEDMASK_USB_READY        0

/** LED mask for the library LED driver, to indicate that an error has occurred in the USB interface. */
#define LEDMASK_USB_ERROR        (LED_CAPS)

#define LEDMASK_CAPS      LED_CAPS
#define LEDMASK_NUMLOCK   0
#define LEDMASK_KEYPAD    0

#define LEDMASK_PROGRAMMING_SRC (LED_CAPS)
#define LEDMASK_PROGRAMMING_DST (LED_CAPS)
#define LEDMASK_MACRO_TRIGGER   (LED_CAPS)
#define LEDMASK_MACRO_RECORD    (LED_CAPS)
#define LEDMASK_ALL ALL_LEDS
#define LEDMASK_NONE 0

void set_all_leds(uint8_t led_mask);

void test_leds(void);

#endif // __KEYPAD_H

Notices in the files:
kinesis.h:
This file is offered under either of the GNU GPL v2 or MIT licences
parts and their libraries:
con-headers-jp: Copyright (C) 2008, Bob Starr
